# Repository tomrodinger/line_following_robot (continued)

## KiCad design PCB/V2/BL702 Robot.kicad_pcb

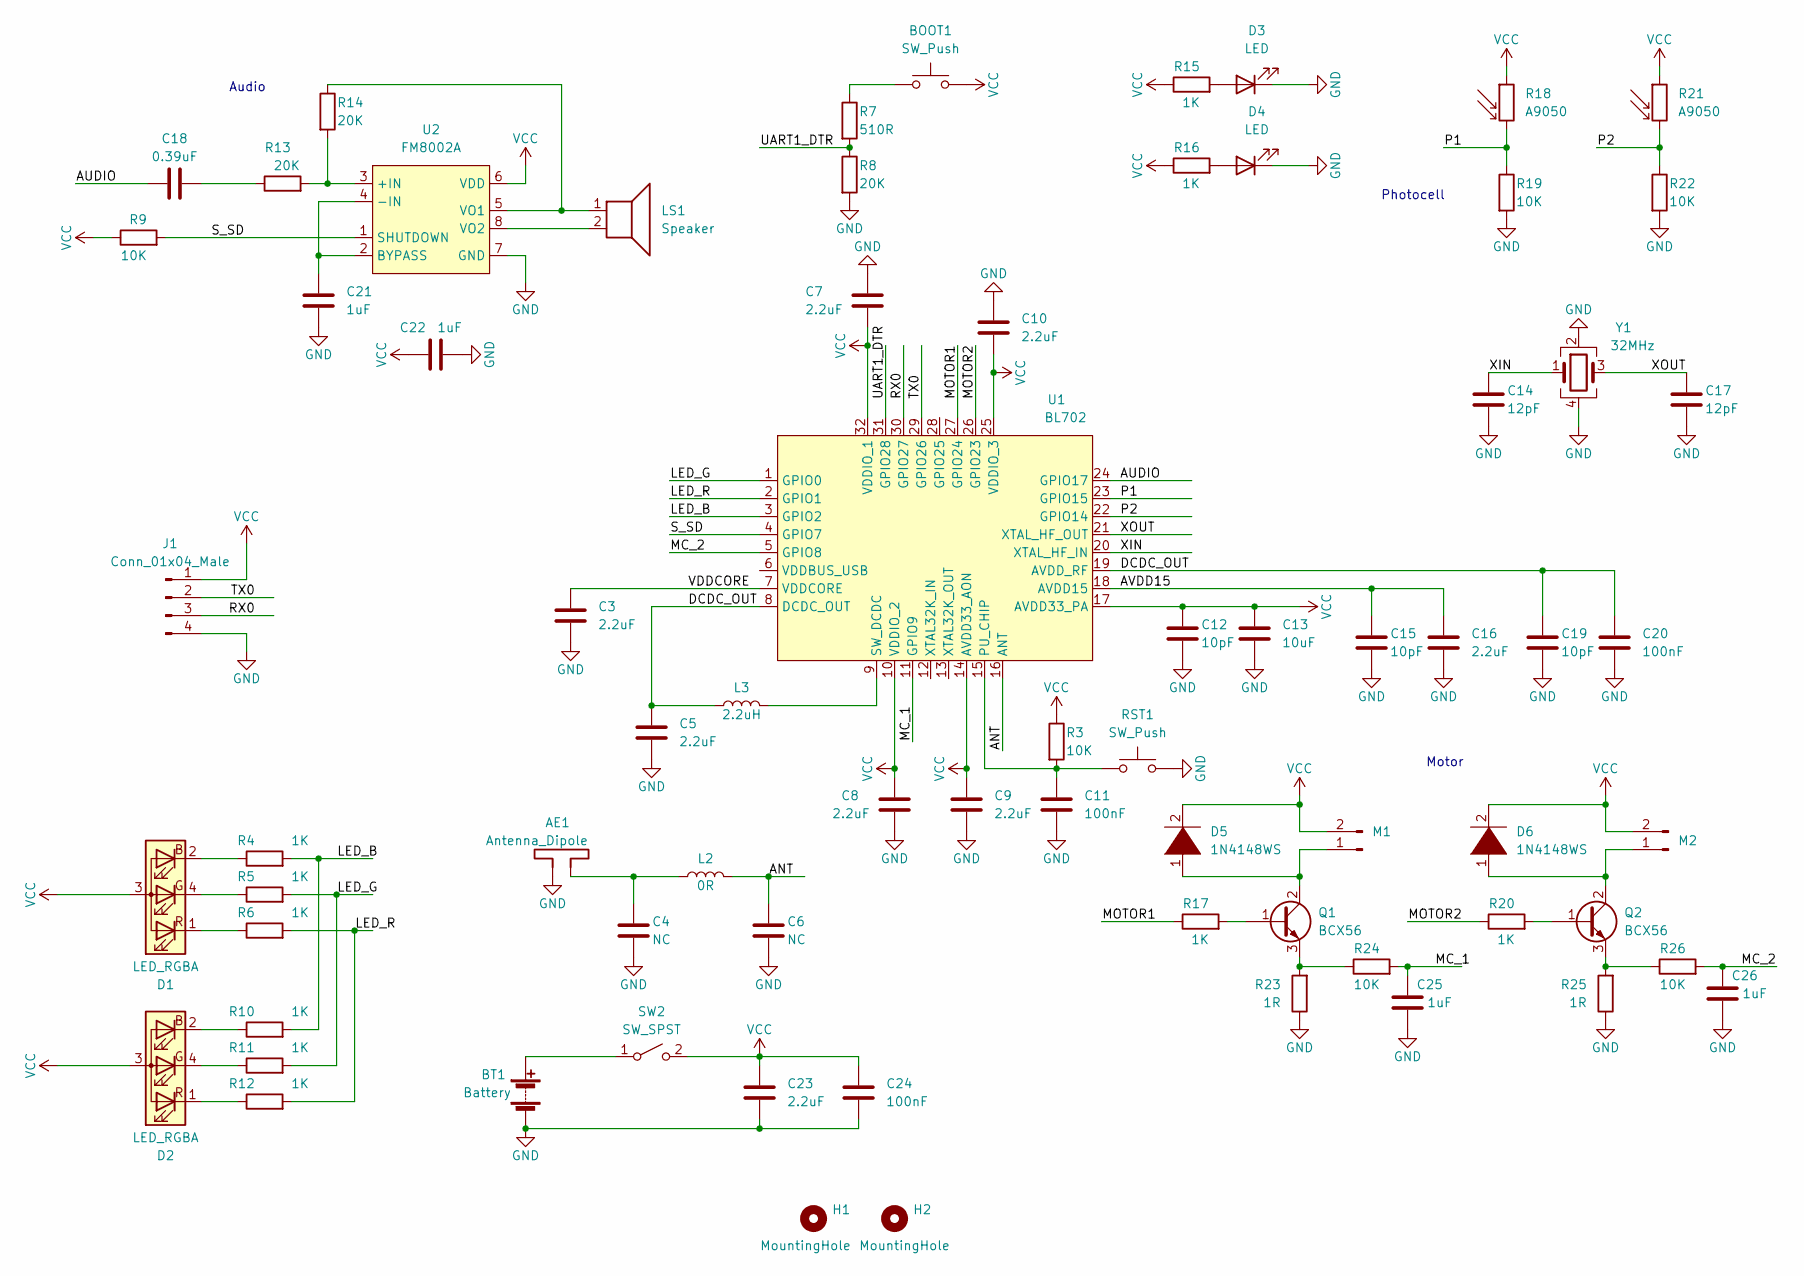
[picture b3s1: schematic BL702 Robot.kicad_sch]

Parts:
AE1: Antenna_Dipole; Texas_SWRA117D_2.4GHz_Right
BOOT1: SW_Push; SW_SPST_EVQPE1; LCSC PN C720477
BT1: Battery; JST_XH_B2B-XH-A_1x02_P2.50mm_Vertical; LCSC C158012
C3, C5, C7, C8, C9, C10, C16, C23: 2.2uF; C_0402_1005Metric; LCSC PN C12530
C4, C6: NC; C_0402_1005Metric
C11, C20, C24: 100nF; C_0402_1005Metric; LCSC PN C307331
C12, C15, C19: 10pF; C_0402_1005Metric; LCSC PN C32949
C13: 10uF; C_0603_1608Metric; LCSC PN C96446
C14: 12pF; C_0402_1005Metric; LCSC PN C1547
C17: 12pF; C_0402_1005Metric
C18: 0.39uF; C_0603_1608Metric
C21, C22, C25, C26: 1uF; C_0603_1608Metric
D1, D2: LED_RGBA; FM-B2020RGBA-HG; LCSC PN C108793
D3, D4: LED; LED_D3.0mm_Horizontal_O1.27mm_Z2.0mm
D5, D6: 1N4148WS; D_SOD-323; LCSC C2128
H1, H2: MountingHole; MountingHole_3mm
J1: Conn_01x04_Male; PinHeader_1x04_P2.54mm_Vertical
L2: 0R; L_0402_1005Metric
L3: 2.2uH; L_0805_2012Metric; LCSC PN C86089
LS1: Speaker; JST_XH_B2B-XH-A_1x02_P2.50mm_Vertical; LCSC C158012
M1, M2: Conn_01x02_Male; JST_XH_B2B-XH-A_1x02_P2.50mm_Vertical; LCSC C158012
Q1, Q2: BCX56; SOT-89-3; LCSC C123402
R3, R9, R19, R22, R24, R26: 10K; R_0402_1005Metric; LCSC PN C25744
R4, R5, R6, R10, R11, R12, R15, R16, R17, R20: 1K; R_0402_1005Metric; LCSC PN C11702
R7: 510R; R_0402_1005Metric; LCSC PN C25123
R8, R13, R14: 20K; R_0402_1005Metric; LCSC PN C25765
R18, R21: A9050; R_LDR_5.0x4.1mm_P3mm_Vertical
R23, R25: 1R; R_1206_3216Metric; LCSC PN C17928
RST1: SW_Push; SW_SPST_EVQPE1; LCSC PN C720477
SW2: SW_SPST; MSK12C02-HB; LCSC C431541
U1: BL702; QFN-32-1EP_4x4mm_P0.4mm_EP2.9x2.9mm; LCSC PN C2874059
U2: FM8002A; SOP-8_3.9x4.9mm_P1.27mm; LCSC C94625
Y1: 32MHz; Crystal_SMD_2016-4Pin_2.0x1.6mm; LCSC PN C255896

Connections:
/ANT: C6.1, L2.2, U1.16 (ANT)
/AUDIO: C18.1, U1.24 (GPIO17)
/AVDD15: C15.1, C16.1, U1.18 (AVDD15)
/DCDC_OUT: C5.1, C19.1, C20.1, L3.1, U1.8 (DCDC_OUT), U1.19 (AVDD_RF)
/LED_B: R4.2, R10.2, U1.3 (GPIO2)
/LED_G: R5.2, R11.2, U1.1 (GPIO0)
/LED_R: R6.2, R12.2, U1.2 (GPIO1)
/MC_1: C25.2, R24.2, U1.11 (GPIO9)
/MC_2: C26.2, R26.2, U1.5 (GPIO8)
/MOTOR1: R17.1, U1.27 (GPIO24)
/MOTOR2: R20.1, U1.26 (GPIO23)
/P1: R18.2, R19.1, U1.23 (GPIO15)
/P2: R21.2, R22.1, U1.22 (GPIO14)
/RX0: J1.3, U1.30 (GPIO27)
/S_SD: R9.2, U1.4 (GPIO7), U2.1 (SHUTDOWN)
/TX0: J1.2, U1.29 (GPIO26)
/UART1_DTR: R7.2, R8.1, U1.31 (GPIO28)
/VDDCORE: C3.1, U1.7 (VDDCORE)
/XIN: C14.1, U1.20 (XTAL_HF_IN), Y1.1
/XOUT: C17.1, U1.21 (XTAL_HF_OUT), Y1.3
GND: AE1.2, BT1.2 (-), C3.2, C4.2, C5.2, C6.2, C7.1, C8.2, C9.2, C10.1, C11.2, C12.2, C13.2, C14.2, C15.2, C16.2, C17.2, C19.2, C20.2, C21.2, C22.2, C23.2, C24.2, C25.1, C26.1, D3.1 (K), D4.1 (K), J1.4, R8.2, R19.2, R22.2, R23.1, R25.1, RST1.2, U1.33, U2.7 (GND), Y1.2, Y1.4; also elsewhere on the board
unnamed: AE1.1, C4.1, L2.1
unnamed 22: BOOT1.1, R7.1; also elsewhere on the board
unnamed: BT1.1 (+), SW2.1 (A)
unnamed 24: C11.1, R3.2, RST1.1, U1.15 (PU_CHIP); also elsewhere on the board
unnamed: C18.2, R13.1
unnamed: C21.1, U2.2 (BYPASS), U2.4 (-IN)
unnamed: D1.1 (RK), R6.1
unnamed: D1.2 (BK), R4.1
unnamed: D1.4 (GK), R5.1
unnamed: D2.1 (RK), R12.1
unnamed: D2.2 (BK), R10.1
unnamed: D2.4 (GK), R11.1
unnamed: D3.2 (A), R15.2
unnamed: D4.2 (A), R16.2
unnamed: D5.1 (K), M1.1, Q1.2 (C)
unnamed: D6.1 (K), M2.1, Q2.2 (C)
unnamed: L3.2, U1.9 (SW_DCDC)
unnamed: LS1.1, R14.1, U2.5 (VO1)
unnamed: LS1.2, U2.8 (VO2)
unnamed: Q1.1 (B), R17.2
unnamed: Q1.3 (E), R23.2, R24.1
unnamed: Q2.1 (B), R20.2
unnamed: Q2.3 (E), R25.2, R26.1
unnamed: R13.2, R14.2, U2.3 (+IN)
VCC: BOOT1.2, C7.2, C8.1, C9.1, C10.2, C12.1, C13.1, C22.1, C23.1, C24.1, D1.3 (A), D2.3 (A), D5.2 (A), D6.2 (A), J1.1, M1.2, M2.2, R3.1, R9.1, R15.1, R16.1, R18.1, R21.1, SW2.2 (B), U1.10 (VDDIO_2), U1.14 (AVDD33_AON), U1.17 (AVDD33_PA), U1.25 (VDDIO_3), U1.32 (VDDIO_1), U2.6 (VDD); also elsewhere on the board

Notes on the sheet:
Photocell
Audio
Motor

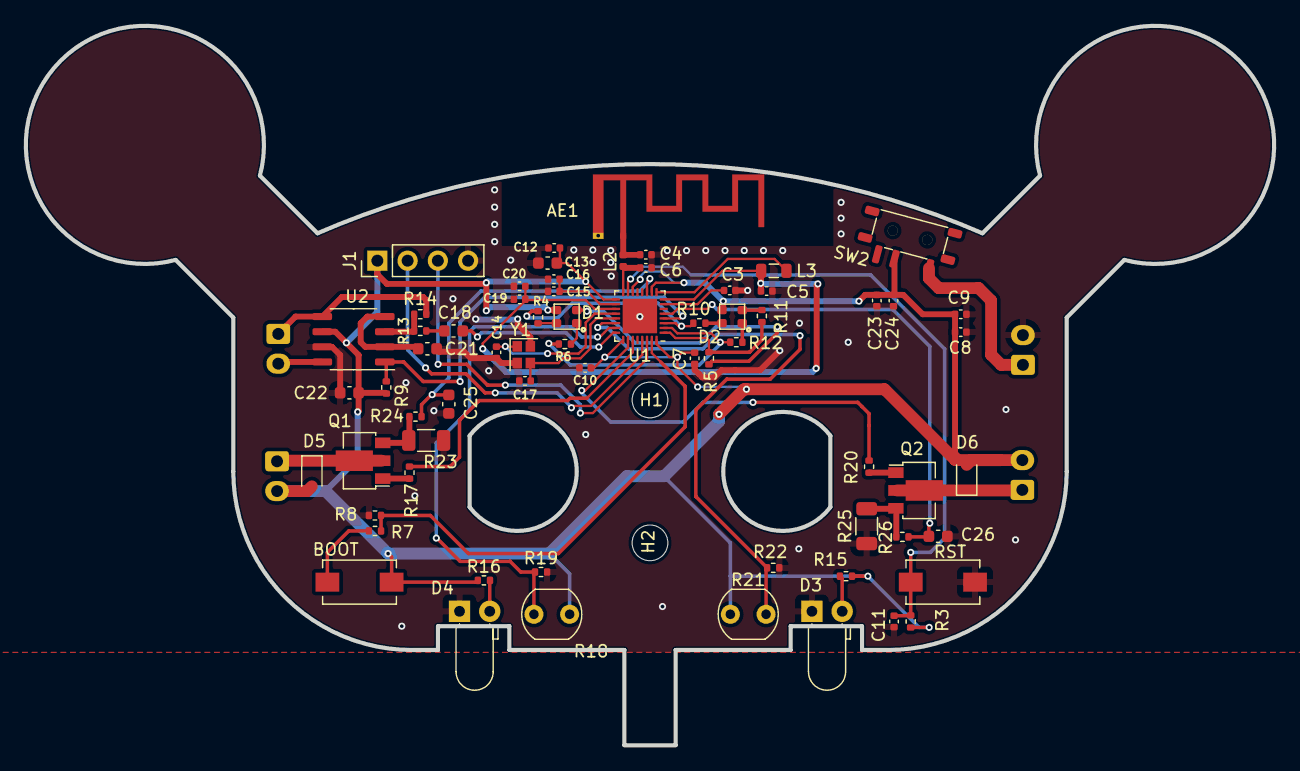
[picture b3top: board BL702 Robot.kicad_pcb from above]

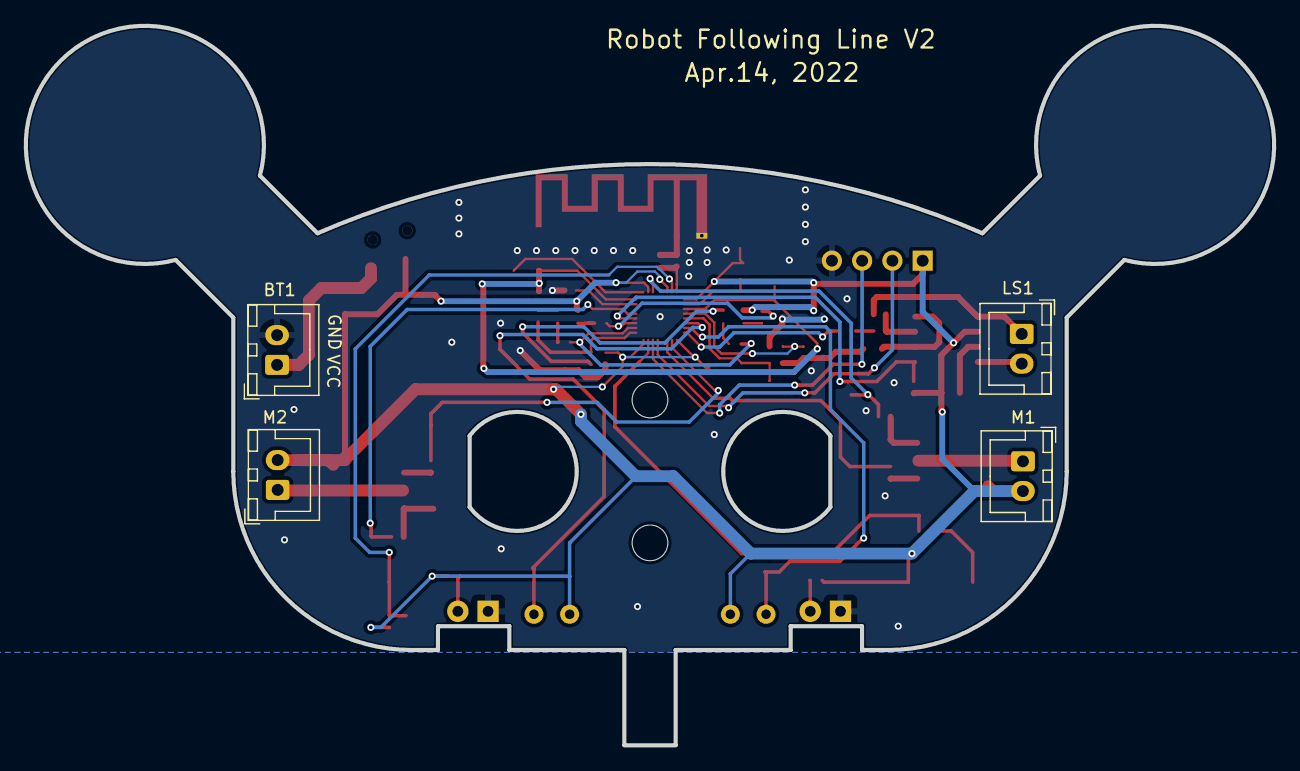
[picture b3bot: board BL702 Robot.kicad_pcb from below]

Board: 2 copper layers, 104.8 x 60.4 mm, 72 parts (4 on the bottom side), 46 nets.

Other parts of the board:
BOOT: SW_Push; SW_SPST_EVQPE1
RST: SW_Push; SW_SPST_EVQPE1

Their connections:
GND: RST.2; also elsewhere on the board
unnamed 22: BOOT.1; also elsewhere on the board
unnamed 24: RST.1; also elsewhere on the board
VCC: BOOT.2; also elsewhere on the board

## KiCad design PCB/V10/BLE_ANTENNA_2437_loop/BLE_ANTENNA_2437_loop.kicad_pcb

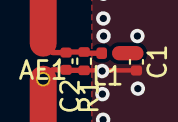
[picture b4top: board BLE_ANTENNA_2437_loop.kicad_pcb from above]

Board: 2 copper layers, 5 parts (0 on the bottom side), 3 nets.

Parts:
AE1: Antenna_Loop; BLE_2437_LOOP_2
C1: 4.8pf NP0; C_0402_1005Metric
C2: 0.6pf NP0; C_0402_1005Metric
L1: 2.5nH; L_0402_1005Metric
R1: 3k0; R_0402_1005Metric

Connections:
GND: AE1.2, C1.2, C2.2, R1.2
unnamed: AE1.1, C2.1, L1.2, R1.1
unnamed: C1.1, L1.1

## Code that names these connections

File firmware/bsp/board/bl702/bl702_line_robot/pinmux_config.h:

/**
 * @file pinmux_config.h
 * @brief
 *
 * Copyright (c) 2021 Bouffalolab team
 *
 * Licensed to the Apache Software Foundation (ASF) under one or more
 * contributor license agreements.  See the NOTICE file distributed with
 * this work for additional information regarding copyright ownership.  The
 * ASF licenses this file to you under the Apache License, Version 2.0 (the
 * "License"); you may not use this file except in compliance with the
 * License.  You may obtain a copy of the License at
 *
 *   http://www.apache.org/licenses/LICENSE-2.0
 *
 * Unless required by applicable law or agreed to in writing, software
 * distributed under the License is distributed on an "AS IS" BASIS, WITHOUT
 * WARRANTIES OR CONDITIONS OF ANY KIND, either express or implied.  See the
 * License for the specific language governing permissions and limitations
 * under the License.
 *
 */
#ifndef _PINMUX_CONFIG_H
#define _PINMUX_CONFIG_H

// <<< Use Configuration Wizard in Context Menu >>>

// <q> GPIO0 <2> [GPIO_FUN_UNUSED//GPIO_FUN_I2S//GPIO_FUN_SPI//GPIO_FUN_I2C//GPIO_FUN_PWM//GPIO_FUN_CAM//GPIO_FUN_UART0_RTS//GPIO_FUN_UART1_RTS//GPIO_FUN_ETHER_MAC//GPIO_FUN_QDEC]
// <i> config gpio0 function
#define CONFIG_GPIO0_FUNC GPIO_FUN_UNUSED

// <q> GPIO1 <2> [GPIO_FUN_UNUSED//GPIO_FUN_I2S//GPIO_FUN_SPI//GPIO_FUN_I2C//GPIO_FUN_PWM//GPIO_FUN_CAM//GPIO_FUN_UART0_CTS//GPIO_FUN_UART1_CTS//GPIO_FUN_ETHER_MAC//GPIO_FUN_QDEC]
// <i> config gpio1 function
#define CONFIG_GPIO1_FUNC GPIO_FUN_UNUSED

// <q> GPIO2 <2> [GPIO_FUN_UNUSED//GPIO_FUN_I2S//GPIO_FUN_SPI//GPIO_FUN_I2C//GPIO_FUN_PWM//GPIO_FUN_CAM//GPIO_FUN_UART0_TX//GPIO_FUN_UART1_TX//GPIO_FUN_ETHER_MAC//GPIO_FUN_QDEC]
// <i> config gpio2 function
#define CONFIG_GPIO2_FUNC GPIO_FUN_UNUSED

// <q> GPIO3 <3> [GPIO_FUN_UNUSED//GPIO_FUN_I2S//GPIO_FUN_SPI//GPIO_FUN_I2C//GPIO_FUN_PWM//GPIO_FUN_CAM//GPIO_FUN_UART0_TX//GPIO_FUN_UART1_TX//GPIO_FUN_ETHER_MAC//GPIO_FUN_QDEC]
// <i> config gpio3 function
#define CONFIG_GPIO3_FUNC GPIO_FUN_PWM

// <q> GPIO4 <4> [GPIO_FUN_UNUSED//GPIO_FUN_I2S//GPIO_FUN_SPI//GPIO_FUN_I2C//GPIO_FUN_PWM//GPIO_FUN_CAM//GPIO_FUN_UART0_TX//GPIO_FUN_UART1_TX//GPIO_FUN_ETHER_MAC//GPIO_FUN_QDEC]
// <i> config gpio4 function
#define CONFIG_GPIO4_FUNC GPIO_FUN_PWM

// <q> GPIO7 <2> [GPIO_FUN_UNUSED//GPIO_FUN_I2S//GPIO_FUN_SPI//GPIO_FUN_I2C//GPIO_FUN_PWM//GPIO_FUN_CAM//GPIO_FUN_USB//GPIO_FUN_UART0_RX//GPIO_FUN_UART1_RX//GPIO_FUN_ETHER_MAC//GPIO_FUN_QDEC]
// <i> config gpio7 function
#define CONFIG_GPIO7_FUNC GPIO_FUN_ADC

// <q> GPIO8 <2> [GPIO_FUN_UNUSED//GPIO_FUN_I2S//GPIO_FUN_SPI//GPIO_FUN_I2C//GPIO_FUN_PWM//GPIO_FUN_CAM//GPIO_FUN_USB//GPIO_FUN_UART0_RTS//GPIO_FUN_UART1_RTS//GPIO_FUN_ETHER_MAC//GPIO_FUN_QDEC]
// <i> config gpio8 function
#define CONFIG_GPIO8_FUNC GPIO_FUN_ADC

// <q> GPIO9 <2> [GPIO_FUN_UNUSED//GPIO_FUN_I2S//GPIO_FUN_SPI//GPIO_FUN_I2C//GPIO_FUN_PWM//GPIO_FUN_CAM//GPIO_FUN_USB//GPIO_FUN_UART0_RTS//GPIO_FUN_UART1_RTS//GPIO_FUN_ETHER_MAC//GPIO_FUN_QDEC]
// <i> config gpio9 function
#define CONFIG_GPIO9_FUNC GPIO_FUN_UNUSED

// <q> GPIO14 <2> [GPIO_FUN_UNUSED//GPIO_FUN_I2S//GPIO_FUN_SPI//GPIO_FUN_I2C//GPIO_FUN_PWM//GPIO_FUN_CAM//GPIO_FUN_USB//GPIO_FUN_UART0_RTS//GPIO_FUN_UART1_RTS//GPIO_FUN_ETHER_MAC//GPIO_FUN_QDEC]
// <i> config gpio14 function
#define CONFIG_GPIO14_FUNC GPIO_FUN_UART0_TX

// <q> GPIO15 <2> [GPIO_FUN_UNUSED//GPIO_FUN_I2S//GPIO_FUN_SPI//GPIO_FUN_I2C//GPIO_FUN_PWM//GPIO_FUN_CAM//GPIO_FUN_USB//GPIO_FUN_UART0_RTS//GPIO_FUN_UART1_RTS//GPIO_FUN_ETHER_MAC//GPIO_FUN_QDEC]
// <i> config gpio15 function
#define CONFIG_GPIO15_FUNC GPIO_FUN_UART0_RX

// <q> GPIO17 <2> [GPIO_FUN_UNUSED//GPIO_FUN_I2S//GPIO_FUN_SPI//GPIO_FUN_I2C//GPIO_FUN_PWM//GPIO_FUN_CAM//GPIO_FUN_USB//GPIO_FUN_UART0_RTS//GPIO_FUN_UART1_RTS//GPIO_FUN_ETHER_MAC//GPIO_FUN_QDEC]
// <i> config gpio17 function
#define CONFIG_GPIO17_FUNC GPIO_FUN_ANALOG

// <q> GPIO18 <2> [GPIO_FUN_UNUSED//GPIO_FUN_I2S//GPIO_FUN_SPI//GPIO_FUN_I2C//GPIO_FUN_PWM//GPIO_FUN_CAM//GPIO_FUN_USB//GPIO_FUN_UART0_RTS//GPIO_FUN_UART1_RTS//GPIO_FUN_ETHER_MAC//GPIO_FUN_QDEC]
// <i> config gpio18 function
#define CONFIG_GPIO18_FUNC GPIO_FUN_ADC

// <q> GPIO19 <2> [GPIO_FUN_UNUSED//GPIO_FUN_I2S//GPIO_FUN_SPI//GPIO_FUN_I2C//GPIO_FUN_PWM//GPIO_FUN_CAM//GPIO_FUN_USB//GPIO_FUN_UART0_RTS//GPIO_FUN_UART1_RTS//GPIO_FUN_ETHER_MAC//GPIO_FUN_QDEC]
// <i> config gpio19 function
#define CONFIG_GPIO19_FUNC GPIO_FUN_ADC

// <q> GPIO21 <2> [GPIO_FUN_UNUSED//GPIO_FUN_I2S//GPIO_FUN_SPI//GPIO_FUN_I2C//GPIO_FUN_PWM//GPIO_FUN_CAM//GPIO_FUN_USB//GPIO_FUN_UART0_RTS//GPIO_FUN_UART1_RTS//GPIO_FUN_ETHER_MAC//GPIO_FUN_QDEC]
// <i> config gpio21 function
#define CONFIG_GPIO21_FUNC GPIO_FUN_ADC

// <q> GPIO23 <2> [GPIO_FUN_UNUSED//GPIO_FUN_I2S//GPIO_FUN_SPI//GPIO_FUN_I2C//GPIO_FUN_PWM//GPIO_FUN_CAM//GPIO_FUN_USB//GPIO_FUN_UART0_RTS//GPIO_FUN_UART1_RTS//GPIO_FUN_ETHER_MAC//GPIO_FUN_QDEC]
// <i> config gpio23 function
#define CONFIG_GPIO23_FUNC GPIO_FUN_UNUSED

// <q> GPIO24 <2> [GPIO_FUN_UNUSED//GPIO_FUN_I2S//GPIO_FUN_SPI//GPIO_FUN_I2C//GPIO_FUN_PWM//GPIO_FUN_CAM//GPIO_FUN_USB//GPIO_FUN_UART0_RTS//GPIO_FUN_UART1_RTS//GPIO_FUN_ETHER_MAC//GPIO_FUN_QDEC]
// <i> config gpio24 function
#define CONFIG_GPIO24_FUNC GPIO_FUN_UNUSED

// <q> GPIO25 <2> [GPIO_FUN_UNUSED//GPIO_FUN_I2S//GPIO_FUN_SPI//GPIO_FUN_I2C//GPIO_FUN_PWM//GPIO_FUN_CAM//GPIO_FUN_USB//GPIO_FUN_UART0_RTS//GPIO_FUN_UART1_RTS//GPIO_FUN_ETHER_MAC//GPIO_FUN_QDEC]
// <i> config gpio25 function
#define CONFIG_GPIO25_FUNC GPIO_FUN_PWM

// <q> GPIO26 <2> [GPIO_FUN_UNUSED//GPIO_FUN_I2S//GPIO_FUN_SPI//GPIO_FUN_I2C//GPIO_FUN_PWM//GPIO_FUN_CAM//GPIO_FUN_USB//GPIO_FUN_UART0_RTS//GPIO_FUN_UART1_RTS//GPIO_FUN_ETHER_MAC//GPIO_FUN_QDEC]
// <i> config gpio26 function
#define CONFIG_GPIO26_FUNC GPIO_FUN_PWM

// <q> GPIO27 <2> [GPIO_FUN_UNUSED//GPIO_FUN_I2S//GPIO_FUN_SPI//GPIO_FUN_I2C//GPIO_FUN_PWM//GPIO_FUN_CAM//GPIO_FUN_USB//GPIO_FUN_UART0_RTS//GPIO_FUN_UART1_RTS//GPIO_FUN_ETHER_MAC//GPIO_FUN_QDEC]
// <i> config gpio27 function
#define CONFIG_GPIO27_FUNC GPIO_FUN_PWM

// <q> GPIO28 <2> [GPIO_FUN_UNUSED//GPIO_FUN_I2S//GPIO_FUN_SPI//GPIO_FUN_I2C//GPIO_FUN_PWM//GPIO_FUN_CAM//GPIO_FUN_USB//GPIO_FUN_UART0_RTS//GPIO_FUN_UART1_RTS//GPIO_FUN_ETHER_MAC//GPIO_FUN_QDEC]
// <i> config gpio28 function
#define CONFIG_GPIO28_FUNC GPIO_FUN_UNUSED

#endif

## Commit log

2022-07-08 These are some of the various iteration of the PCB design
2022-07-08 updated last file
2022-07-22 Commit bl702 sdk and line following robot application
2022-07-23 Uploaded first firmware binary for robot to follow line built at commit c508ea9e
2022-08-02 bl702_line_robot: Added pin and clock configuration for DAC
2022-08-02 hal_dac: Added workaround for dac to run DMA on channel 1
2022-08-02 line_robot: Added audio support
2022-08-02 firmware_releases: Added binary to support audio
2022-08-03 Makefile: Set default BLE library as 0 central and 1 peripheral with scan feature
2022-08-03 partition: Changed address of application firmware
2022-08-03 line_robot: Added to support jumping back into bootloader and decrease volume of audio
2022-08-03 robot_bootloader: Added bootloader for line following robot
2022-08-03 boot_script: Update to support ble update for robot
2022-08-03 firmware: Added new firmware with bootloader support
2022-08-04 line_robot: Sync BLE information between application and bootloader
2022-08-04 Update firmware release to sync BLE information between app and bootloader
2022-08-04 line_robot: Reduce audio and speed to avoid crash issue due to battery
2022-08-06 line_robot: Correct BLE device name
2022-08-06 bootloader: Increase boot timeout and correct BLE device name
2022-08-06 Upload android application to update device
2022-08-06 Update firmware binaries based on changes
2022-08-06 Upload binary with medium and max volume
2022-08-25 Update new android app from python and bootloader
2022-09-23 line_robot: Changed pwm frequency to 20khz
2022-09-23 robot_bootloader: Changed ble protocol to make it more stable
2022-09-23 Commit new firmware and bootloader binaries
2022-09-29 bootloader: Use a flag in ram to decide time for waiting ble connection
2022-09-29 bootloader: Added a header for ble package to avoid missing package in ble network
2022-09-30 Update firmware release binaries
2022-10-11 Update python script to adapt with latest bootloader
2022-10-20 Add files via upload
    loop antenna and optimized routing
2023-02-07 Update binaries using internal osc
2023-02-13 bl702_line_robot: Enable wdg and select clock source as 32k for it.
2023-02-13 hal_wdt: Correct writing to wdg compare register
2023-02-13 interrupt: Added option to reset if trap interrupt happens
2023-02-13 line_robot: Do reset after 0.5s since received enter bootloader request
2023-02-13 robot_bootloader: Update ble interface to make it more stable and added wdg to reset if bootloader hangs.
2023-02-13 upgrade_firmware.py: Updated to adapt with latest code
2023-02-13 Update binaries for new release
2023-02-13 Update android apk for release
2023-02-15 Update android app support to upload line_robot and lego_train
2023-03-22 Adding version 10 of the Robot PCB
2023-04-11 Add the PRODUCT_DATA.json file for automatic web site generation
2023-04-11 Adding the schematic for V10 PCB
2023-05-03 Updating the product data
2023-05-17 Delete PRODUCT_DATA.json
    Replaced by PRODUCT_DATA.yaml
2023-05-18 front.jpg
    line following robot's pictures
2023-05-18 updating v1
    pictures of Line Following Robot
2023-05-18 Update the picture for v1
    top 1 photo, May 18, 2023
2023-05-18 Update the picture for v1
    top 1.jpg May 18, 2023
2023-05-18 updating v10
2023-05-28 line_robot: Update draft robot detection
2023-05-28 firmware_releases: Update new release with draft robot detection
2023-06-01 Checking in V11 of PCB and also updating PRODUCT_DATA.yaml to add V11
2023-07-23 Update line_robot application with draft detection feature
2023-07-23 Create new release for robot draft detection
2023-07-23 Update draft detection feature with audio
2023-07-23 Update release with binary having audio
2023-07-24 Upload firmware list json file used to upload firmware
2023-07-24 Upload android app used to update firmware
2023-08-06 audio: Use ring buffer to improve performance and correct gain logic
2023-08-06 Commit test firmware for new pcb
2023-08-06 Update firmware list with new binaries
2023-08-09 Adding the PCB files for V12
2023-08-09 Update PRODUCT_DATA.yaml
    Added V12 version
2023-08-09 Updated V10 picture's link
2023-08-18 Updated new binary with correcting calibration method
2023-08-19 Updated new binaries with duty cycle as 50% and 25%
2023-08-19 firmware_list.json: Remove old releases
2023-08-19 Improve detection distance
2023-08-19 Update new binary with detection distance improved
2023-08-20 Improve robot detection and line tracking
2023-08-20 Upload new release with improving line tracking and robot detection
2023-08-23 Uploaded test binary
2023-08-25 Upload test binaries with duty cycle as 35% and 42%
2023-08-31 Update new binary with duty cycle as 30%
2023-09-12 Upload new binaries support duty cycle as 60% and 70%
2023-09-19 Move V10 pictures to the folder V10
2023-09-19 Update PRODUCT_DATA.yaml picture
2023-09-19 Rename the files
2023-09-19 Add new folders
2023-09-19 Add pictures
2023-09-19 Update PRODUCT_DATA.yaml picture V11
2023-09-19 Add files
2023-09-19 Update PRODUCT_DATA.yaml V12 picture
2023-09-19 Update PRODUCT_DATA.yaml V11 picture
2023-09-20 Adding an embedded link to the web site template for the line following robot.
2023-09-25 Updating to the proper video
2023-10-08 Correct robot behavior with new design
2023-10-08 Update new release to support new pcb
2023-10-12 Support high spike detection and correct robot line following
2023-10-16 sensor.c: Added function to clear ir calibration values and detect other robot while calib ir
2023-10-16 robot.c: Used high spike detection to reduce speed so that ir sensor can detect other robot
2023-10-16 ble_app.c: Corrected ble_send
2023-10-16 Fixed compilation warnings
2023-10-16 Update new release to improve line following and motor high spike detection
2023-10-17 added the video link
2023-10-17 added the second picture
2023-10-17 Upload test binaries for latest pcb
2023-10-18 Uploaded new test binaries related to speed
2023-10-20 Correct calibration method of robot
2023-10-20 Commit new release which support all of features (based on test3 20231018)
2023-11-02 added the video
2023-11-02 update html template to use the picture and video
2023-11-03 add working pictures and video
2023-11-04 updating the video
2023-11-05 updated the video and added a picture
2023-12-09 remove tutorial from line following robot
2023-12-10 removed user manaul
